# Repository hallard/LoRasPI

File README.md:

Raspberry PI Lora Gateway/Node for RFM92/95/96/98/69HCW Modules
===============================================================

This shield is used to hold HopeRF [Lora module][4] Software with Raspbery PI. it has just few minimal features and it's working for [TTN network][1]. 

I tweaked the [Single LoraWan Gateway][5] to get it working out of the box. It should also works with [HAB Supplies Lora Gateway][7] (same pinout), see this excellent [Dave's article][6].

This shield can also act as a LoraWAN Node/gateway using this custom dedicated software    
- RPI version of [LMIC][9] stack. This LMIC is working with this shield, see [readme][13] of repo.
- for RF69 networks using the excellent [RadioHead][10] customized library. This version is working with this shield, see [readme][12] of library.

As you can see, this shield is small but can do a lot but if you need a shield with more features (modules) on same board, I've designed a more featured one. It's called RPI Lora Gateway, you can go [here][11] to see it.

Features
========
- Placement for RFM92/95/96/98 Lora module or RFM69HCW classic module
- Placement for choosing single Wire, SMA or u-FL Antenna type
- 2 x LED LED for visual indication

**New in Version 1.2a**

- V1.2 CS trace missing fixed

**New in Version 1.2**

- R3 Error corrected, it's now a Pull Down
- DIO5 connection to GPIO24 removed, not used
- 2nd led is now connected to GPIO24 instead of CS line

**Error in V1.2, one small trace on CS (CE0 and CE1) signal is missing, fixed in V1.2a**, I really apologize for this error, Eagle beginner error, ALWAYS place junction on schematic, because sometime it looks like connected but it's not!

Here is how to fix this V1.2 trace missing

Clean Way (experienced soldering user)
---------------------------------------
With a small cutter or tool remove silk to bring via copper visible, then solder a tiny wire from CS pad to Via as follow (in green)

Easy Way
--------
Just route the CE0 or CE1 signal with a small wire dirctly to RFM9x module as follow

Use purple wire if you want to use CE0 and Cyan for CE1

**New in Version 1.1**

- Reduced board width so it can be soldered on 2x40 pins connector to expose other GPIOs
- Added DIO1 and DIO2 OR'ed with DIO0 and 1N4148 diode to conform LIMC stack
- Better ground plane isolation
- Added some via on RF part 

I'm waiting now new V1.1 and V1.2 boards from OSHPark and PCBs.io, so I didn't fully tested V1.1/V1.2 yet, I will update ASAP.

I discovered a design error on V1.1, R3 resistor should be a pull down resistor and not a pull up, so **you should not populate R3, do not place it**, it's not a real problem since software will activate pull down of the BCM2835 controller but it's corrected in V1.2

~~I'm waiting boards V1.0~~ Boards arrived from OSHPark, all is working as expected (V1.0). ~~so I didn't fully tested them yet, I will update ASAP~~.

Detailed Description
====================

Look at the schematics for more informations.

SPI connexion is classic (MOSI/MISO/CLK), Chip Select can be connected to CE0 or CE1 of PI depending on bord solder PAD jumper.
Take care that by default it's connected to CE0 (wired) so you don't have to do anything. If you want to connect to CE1 you'll need to cut CE0 trace on the PCB (on the solder pad).

Only One GPIO needed for DIO0/DIO1/DIO2 (OR made with 3 diodes and one resistor R3) that will make this board fully compatible with current LIMC implementation, even if I've done a software fix which works with no interrupt. Only Needed for Lora modules, if you're using RFM69HCW and and to use IRQ just place D0 and R3.

~~Other pins that may need be adapted into code (for example if you use TTN network gateway code) according to the following pinout~~ This [Single LoraWan Gateway][5] has been tweaked and works right out of the box.

Detailed Description
====================

**Since V1.2**
```
Raspberry PI   RFM9x Module 1
   GPIO22  <---->  Reset
   GPIO25  <---->  DIO0 OR DIO1 OR DIO2 (Hardware OR done with 1N4148 Diode and R3)

Raspberry PI   On Board LEDS
   GPIO23  <---->  LED D3 TX/RX
   GPIO24  <---->  LED D4 LED
```

**V1.0 and V1.1**
```
Raspberry PI   RFM9x Module 1
   GPIO22  <---->  Reset
   GPIO25  <---->  DIO0 OR DIO1 OR DIO2 (Hardware OR done with 1N4148 Diode and R3)
   GPIO24  <---->  DIO5 (Ready)

Raspberry PI   On Board LEDS
   GPIO23  <---->  LED D1 TX/RX
CE0 or CE1 <---->  LED D2 CS
```

### Schematic  

### Boards  

### Assembled boards (V1.0)

V1.0 connected to Raspberry PI.

You can order the PCB of this board at [OSHPARK][3] (V1.1) or new V1.2a at [PCBs.io][8]. PCBs.io give me some reward when you order my designed boards from their site. This is pretty good, because I can use these rewards to create and design new boards and order boards for a discounted price and share new boards. So if you don't care about PCB manufacturer please use PCBs.io.

##License

This work is licensed under a [Creative Commons Attribution-NonCommercial-ShareAlike 4.0 International License](https://creativecommons.org/licenses/by-nc-sa/4.0/).
If you want to do commercial stuff with this project, please contact [CH2i company](https://ch2i.eu/en#support) so we can organize an simple agreement.

##Misc

See news and other projects on my [blog][2] 

[1]: https://staging.thethingsnetwork.org/wiki/Hardware/Gateways/DIY 
[2]: https://hallard.me
[3]: https://oshpark.com/shared_projects/BVwV2j3b
[4]: http://www.hoperf.com/rf_transceiver/lora/
[5]: https://github.com/hallard/single_chan_pkt_fwd
[6]: http://www.daveakerman.com/?p=1719
[7]: https://store.uputronics.com/index.php?route=product/product&search=lora&product_id=68
[8]: https://PCBs.io/share/4q9kM
[9]: https://github.com/hallard/arduino-lmic/tree/rpi
[10]: https://github.com/hallard/RadioHead
[11]: https://github.com/hallard/RPI-Lora-Gateway
[12]: https://github.com/hallard/RadioHead/blob/master/README.md
[13]: https://github.com/hallard/arduino-lmic/blob/rpi/README.md

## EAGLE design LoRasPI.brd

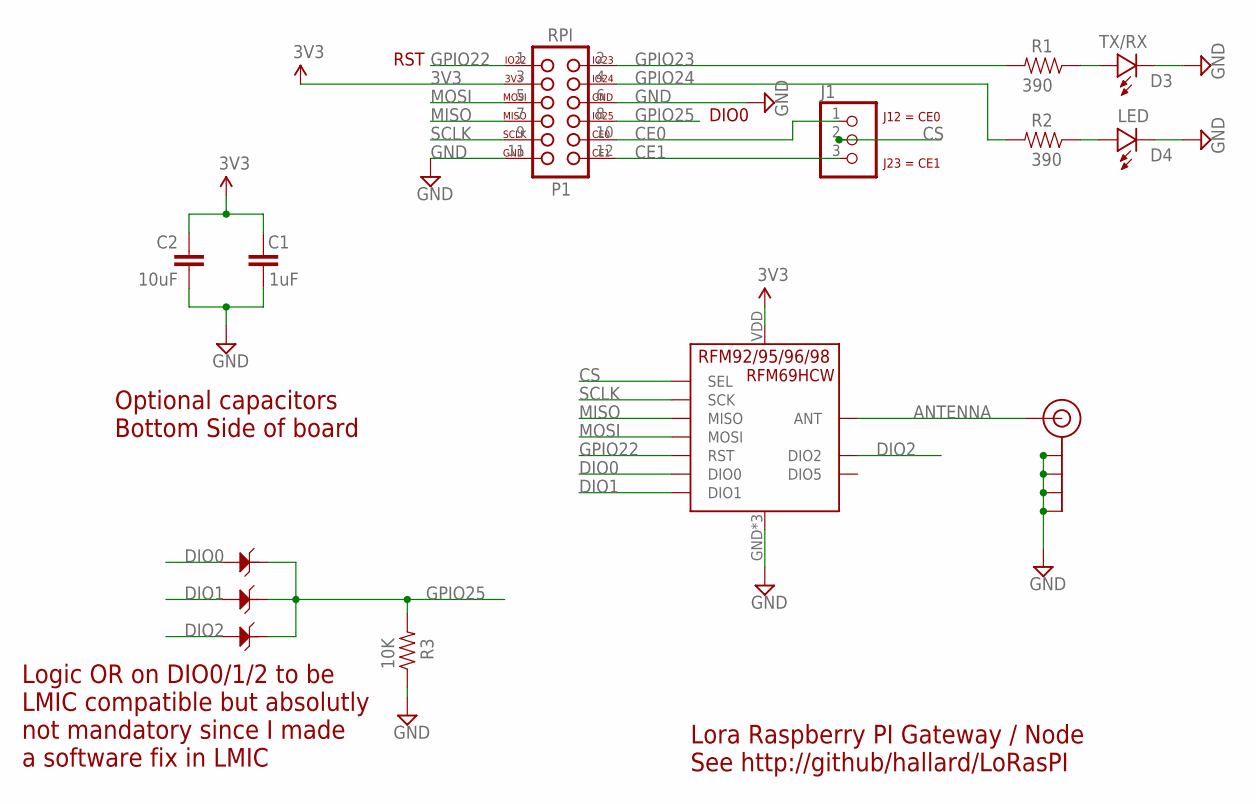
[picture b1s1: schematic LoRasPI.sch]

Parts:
C1: 1uF; 0805-CAP-LARGEPADS
C2: 10uF; 0805-CAP-LARGEPADS
D0, D1, D2: 1N4148; SOD123-2.7X1.6
D3: TX/RX; 0805-LED-LARGEPADS
D4: LED; 0805-LED-LARGEPADS
HOPE-RF: RFM92/95/96/98; RFM95
J1: JUMPER_1X30805; JP3_0805
J$1: ANTENNATINY; SMA_UFL_PAD_TINY
R1, R2: 390; 0805-RES
R3: 10K; 0805-RES
U$2: RASPBERRY_PI_2X6_BOTTOM; 2X06_LOCK

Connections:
3V3: C1.2, C2.2, HOPE-RF.VDD (VCC), U$2.3 (17)
ANTENNA: HOPE-RF.ANT, J$1.ANT1 (SIGNAL), J$1.ANT2 (SIGNAL), J$1.ANT3 (SIGNAL)
CE0: J1.1, U$2.10 (24)
CE1: J1.3, U$2.12 (26)
CS: HOPE-RF.NSS (SEL), J1.2
DIO0: D0.1, HOPE-RF.DIO0
DIO1: D1.1, HOPE-RF.DIO1
DIO2: D2.1, HOPE-RF.DIO2
GND: C1.1, C2.1, D3.MINUS, D4.MINUS, HOPE-RF.GND, HOPE-RF.GND1 (GND), HOPE-RF.GND2 (GND), J$1.GND1 (GND), J$1.GND2 (GND), J$1.GND3 (GND), J$1.GND4 (GND), R3.1, U$2.6 (20), U$2.11 (25)
GPIO22: HOPE-RF.RST, U$2.1 (15)
GPIO23: R1.2, U$2.2 (16)
GPIO24: R2.2, U$2.4 (18)
GPIO25: D0.2, D1.2, D2.2, R3.2, U$2.8 (22)
MISO: HOPE-RF.MISO, U$2.7 (21)
MOSI: HOPE-RF.MOSI, U$2.5 (19)
unnamed: D3.PLUS, R1.1
unnamed: D4.PLUS, R2.1
SCLK: HOPE-RF.SCK, U$2.9 (23)

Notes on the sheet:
Lora Raspberry PI Gateway / Node
See http://github/hallard/LoRasPI
Optional capacitors Bottom Side of board
RFM69HCW
Logic OR on DIO0/1/2 to be LMIC compatible but absolutly not mandatory since I made a software fix in LMIC
RST
DIO0

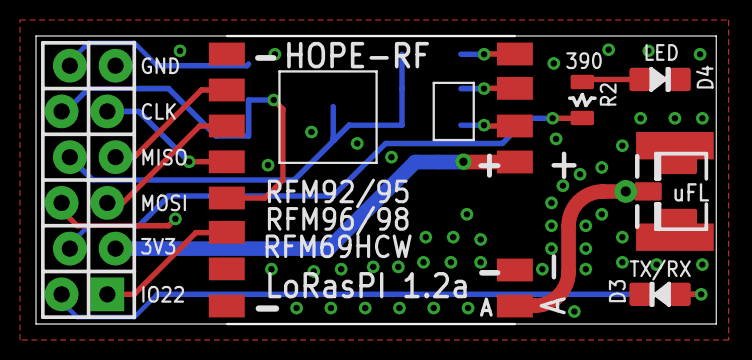
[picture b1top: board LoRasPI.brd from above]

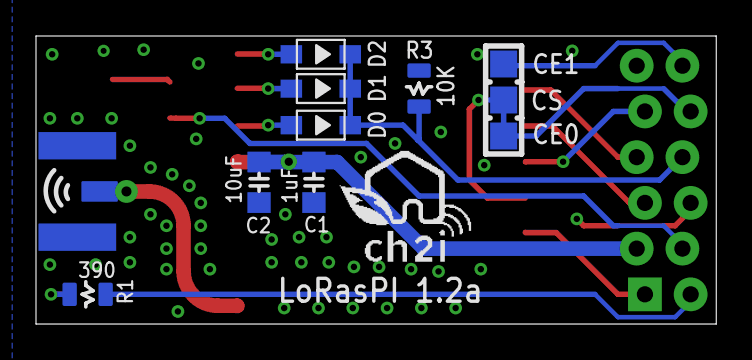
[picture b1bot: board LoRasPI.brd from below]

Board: 2 copper layers, 37.8 x 16.0 mm, 15 parts (9 on the bottom side), 18 nets.

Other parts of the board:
U$4: LOGO_CH2I_75MM

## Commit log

2016-06-03 :tada: Added .gitattributes & .gitignore files
2016-06-03 Creation
2016-06-03 Updated OSHPArk shared project link
2016-06-03 Added warning on CE0/CE1 solder pad
2016-06-16 small typo in 'Optionnal'
2016-06-25 Moved to images folder
2016-06-25 Updated doc
2016-06-25 Added link to SC Gateway
2016-06-27 Added pictures of assembled boards
2016-08-06 Bump to V1.1
2016-08-06 Typo
2016-08-06 Added R3 description
2016-08-06 Added some doc
2016-08-06 Added link to RPI Lora Gateway
2016-08-22 Added warning on R3 error
2016-08-22 Version 1.2
2016-09-21 Added software links
2016-10-03 V1.2a, fixed missing trace
2016-10-03 Creation V1.2
2016-10-03 Added how to fi V1.2 missing trace
2016-10-03 V1.2 Assembled
2016-10-03 Presentation
2016-10-03 Updated PCBs.io link
2017-11-22 Update README.md
    labels of on board LEDs corrected
2026-04-29 Add CC BY-NC-SA 4.0 LICENSE and update README

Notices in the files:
parts and their libraries:
SparkFun-Aesthetics: Licensing: Creative Commons ShareAlike 4.0 International - https://creativecommons.org/licenses/by-sa/4.0
